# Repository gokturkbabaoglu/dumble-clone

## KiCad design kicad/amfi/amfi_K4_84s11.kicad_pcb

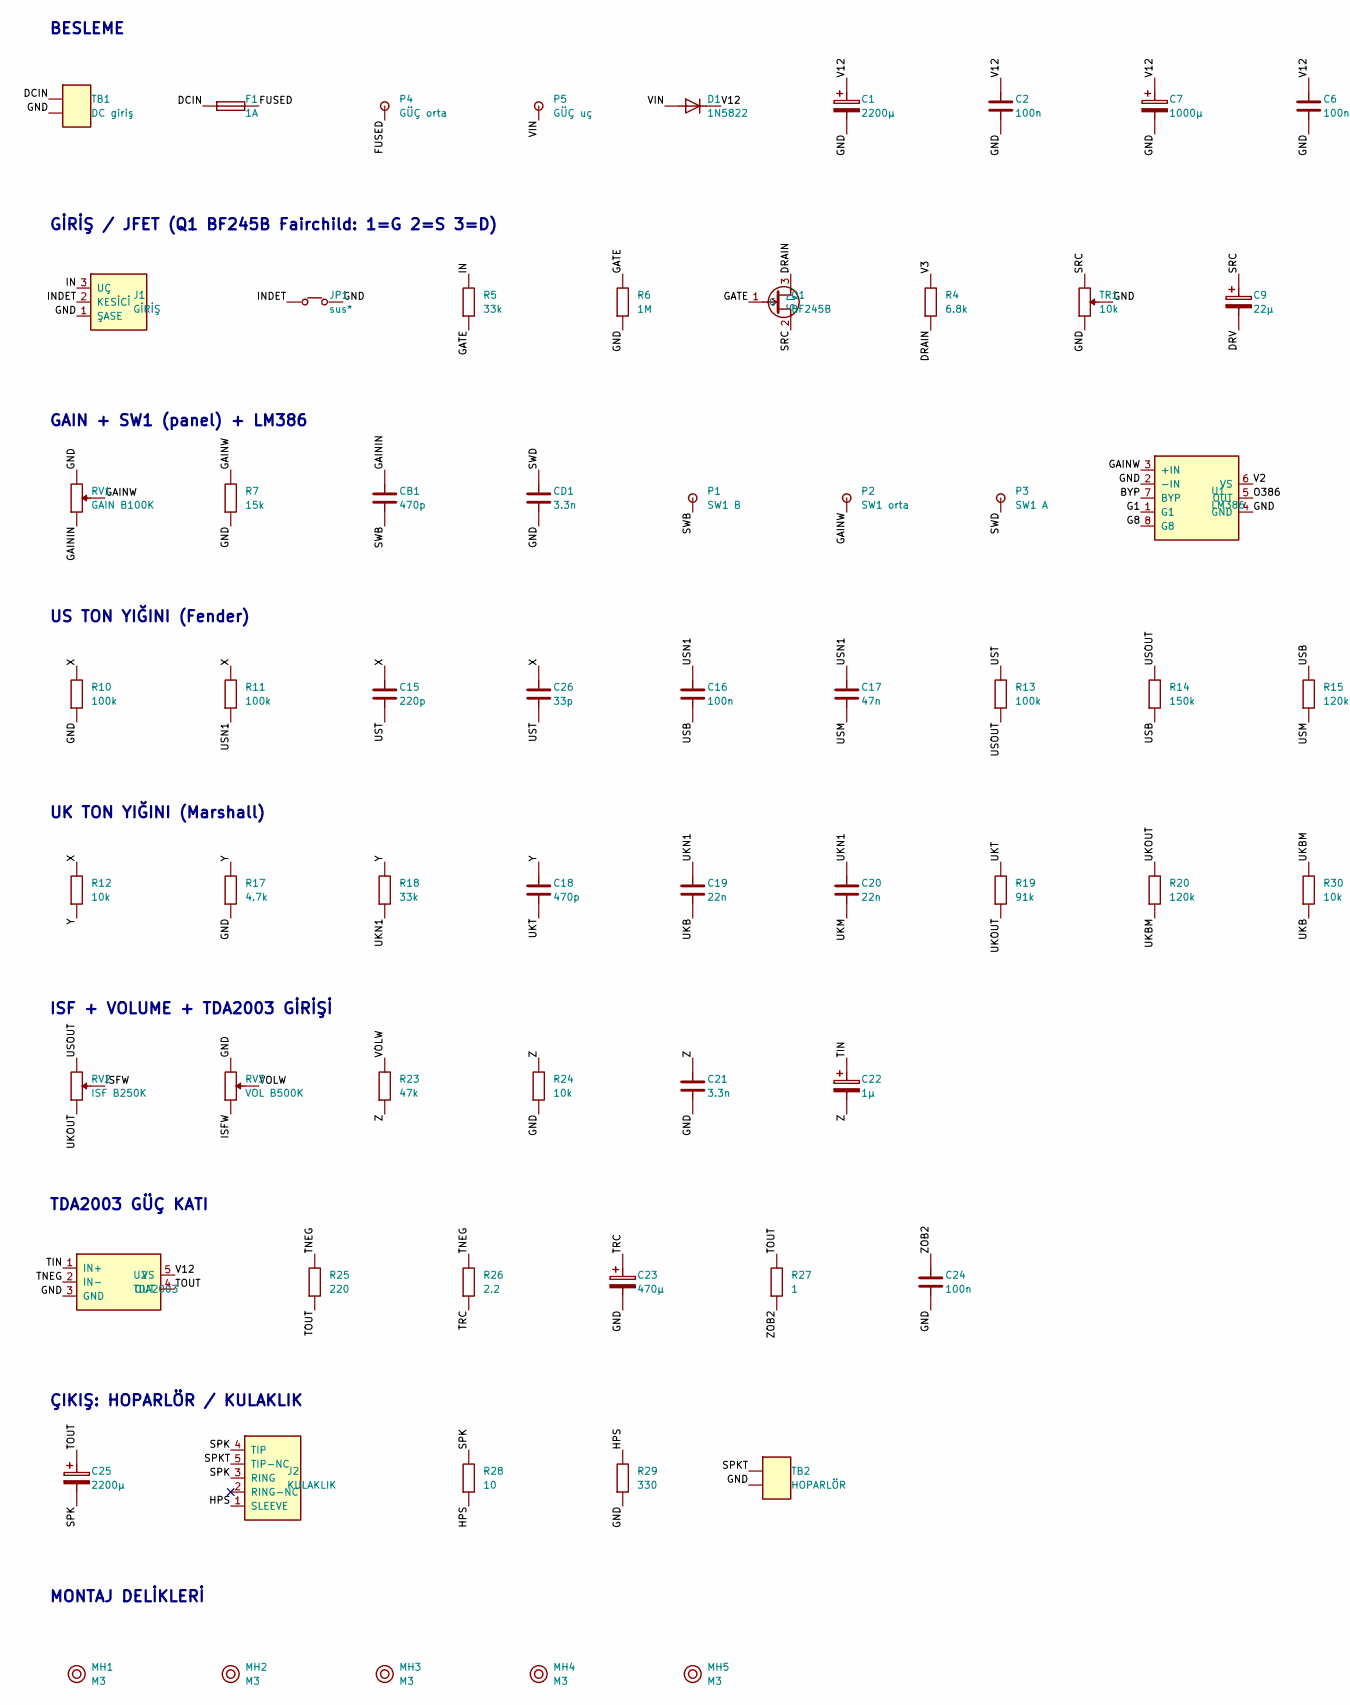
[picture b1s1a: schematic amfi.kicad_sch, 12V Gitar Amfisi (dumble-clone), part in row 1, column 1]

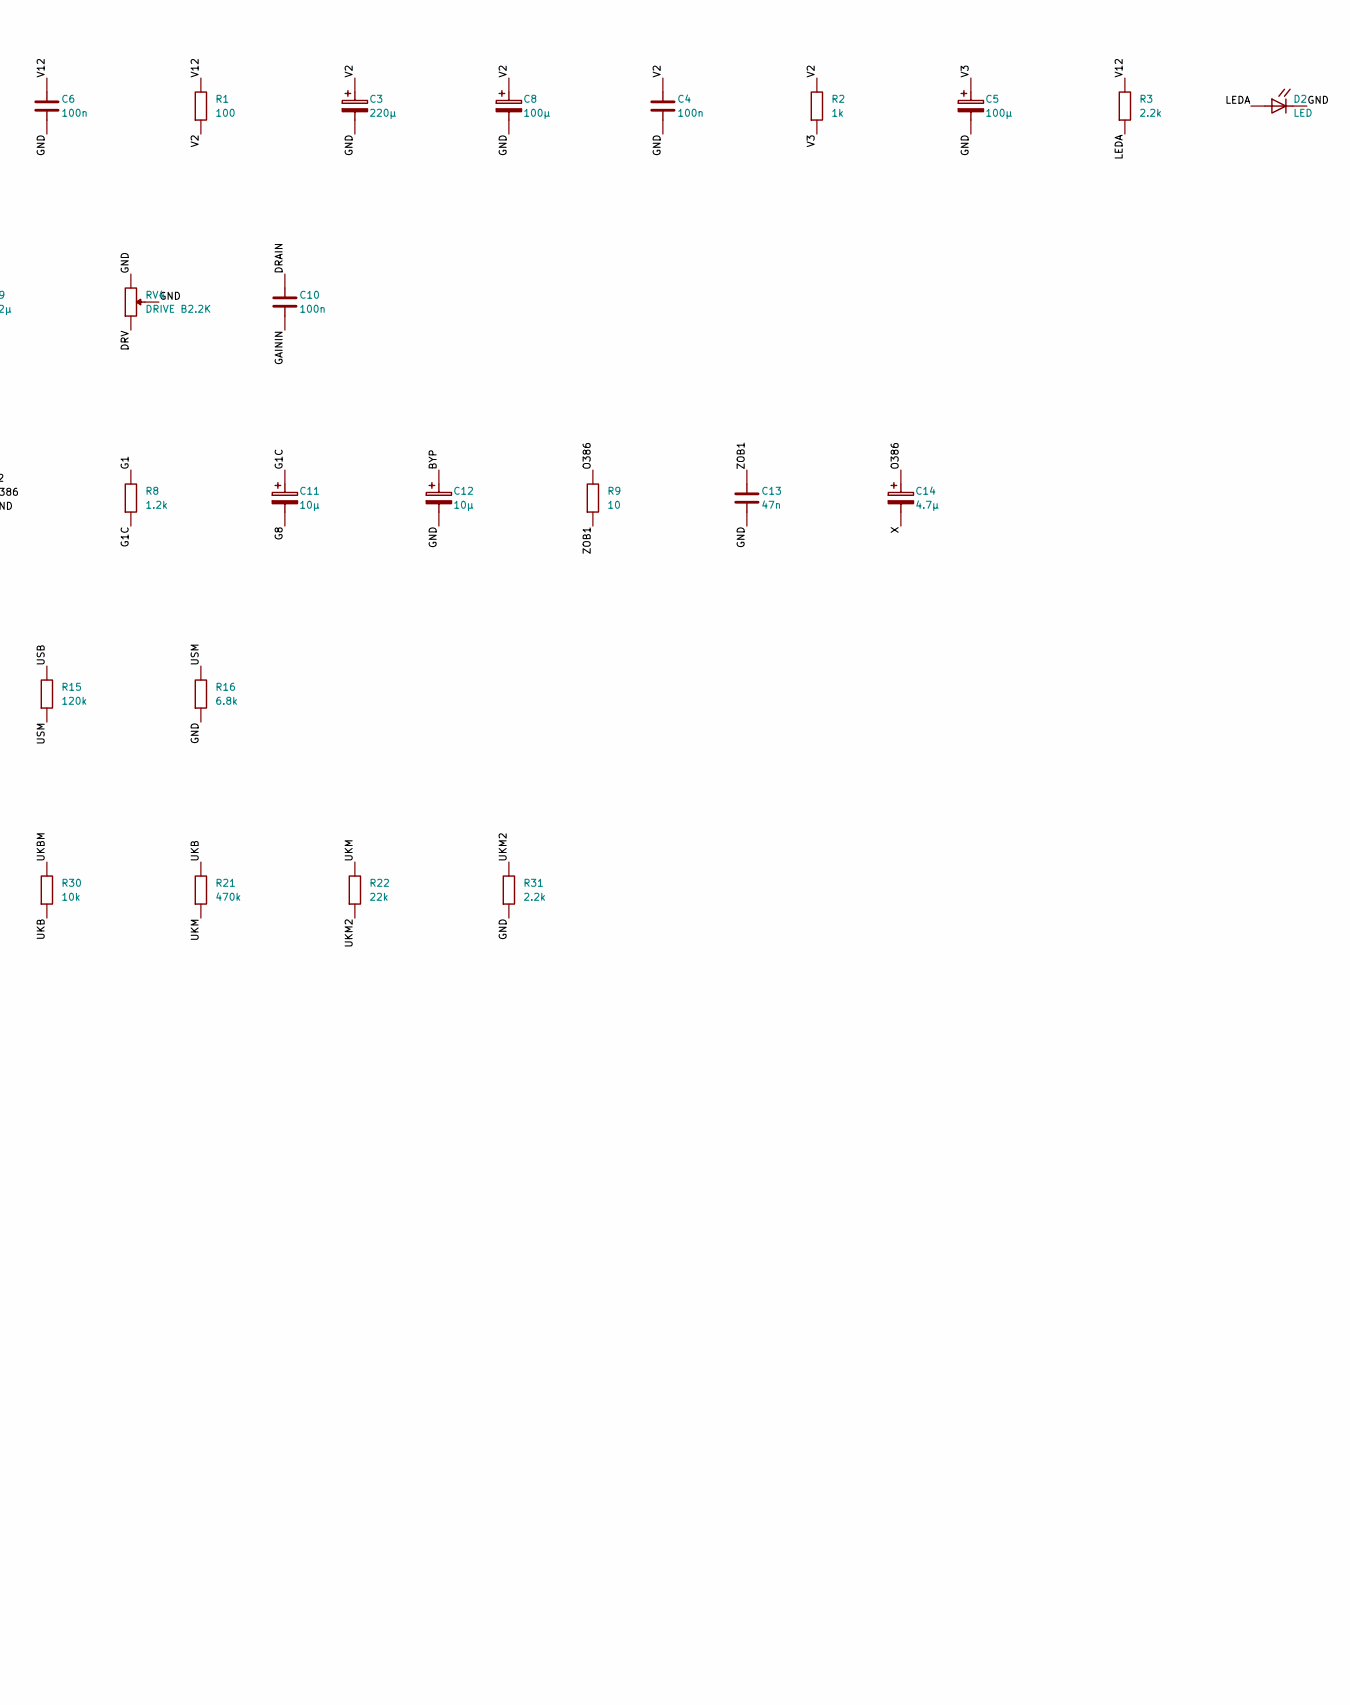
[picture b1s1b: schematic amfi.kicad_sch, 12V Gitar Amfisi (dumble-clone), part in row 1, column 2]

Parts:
C1, C25: 2200µ; CP_D12.5_P5
C2, C4, C6, C10, C16, C24: 100n; C_Film_P5.08
C3: 220µ; CP_D6.3_P2.5
C5, C8: 100µ; CP_D5_P2
C7: 1000µ; CP_D10_P5
C9: 22µ; CP_D5_P2
C11, C12: 10µ; CP_D5_P2
C13, C17: 47n; C_Film_P5.08
C14: 4.7µ; CP_D5_P2
C15: 220p; C_Disc_P5.08
C18: 470p; C_Disc_P5.08
C19, C20: 22n; C_Film_P5.08
C21: 3.3n; C_Film_P5.08
C22: 1µ; CP_D5_P2
C23: 470µ; CP_D8_P3.5
C26: 33p; C_Disc_P5.08
CB1: 470p; C_Disc_P5.08
CD1: 3.3n; C_Film_P5.08
D1: 1N5822; DO201_P15.24
D2: LED; LED_5mm_Dik90
F1: 1A; Sigorta_23x9_P10
J1: GİRİŞ; Jak_6.35_Mono
J2: KULAKLIK; PJ-324M
JP1: sus*; Jumper_P5.08
MH1, MH2, MH3, MH4, MH5: M3; MH_M3
P1: SW1 B; Pad_Kablo
P2: SW1 orta; Pad_Kablo
P3: SW1 A; Pad_Kablo
P4: GÜÇ orta; Pad_Kablo
P5: GÜÇ uç; Pad_Kablo
Q1: BF245B; TO92_Inline_GSD
R1: 100; R_P10.16
R2: 1k; R_P10.16
R3, R31: 2.2k; R_P10.16
R4, R16: 6.8k; R_P10.16
R5, R18: 33k; R_P10.16
R6: 1M; R_P10.16
R7: 15k; R_P10.16
R8: 1.2k; R_P10.16
R9, R28: 10; R_P10.16
R10, R11, R13: 100k; R_P10.16
R12, R24, R30: 10k; R_P10.16
R14: 150k; R_P10.16
R15, R20: 120k; R_P10.16
R17: 4.7k; R_P10.16
R19: 91k; R_P10.16
R21: 470k; R_P10.16
R22: 22k; R_P10.16
R23: 47k; R_P10.16
R25: 220; R_P10.16
R26: 2.2; R_P10.16
R27: 1; R_P10.16
R29: 330; R_P10.16
RV1: GAIN B100K; Pot_WH148_16mm
RV2: ISF B250K; Pot_WH148_16mm
RV3: VOL B500K; Pot_WH148_16mm
RV4: DRIVE B2.2K; Pot_WH148_16mm
TB1: DC giriş; Klemens_2_P5.08
TB2: HOPARLÖR; Klemens_2_P5.08
TR1: 10k; Trim_3296W
U1: LM386; DIP8_Socket
U2: TDA2003; Pentawatt_V

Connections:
BYP: C12.1 (+), U1.7 (BYP)
DCIN: F1.1, TB1.1
DRAIN: C10.1, Q1.3 (D), R4.2
DRV: C9.2 (-), RV4.3
FUSED: F1.2, P4.1
G1: R8.1, U1.1 (G1)
G1C: C11.1 (+), R8.2
G8: C11.2 (-), U1.8 (G8)
GAININ: C10.2, CB1.1, RV1.3
GAINW: P2.1, R7.1, RV1.2, U1.3 (+IN)
GATE: Q1.1 (G), R5.2, R6.1
GND: C1.2 (-), C2.2, C3.2 (-), C4.2, C5.2 (-), C6.2, C7.2 (-), C8.2 (-), C12.2 (-), C13.2, C21.2, C23.2 (-), C24.2, CD1.2, D2.2 (K), J1.1 (ŞASE), JP1.2, R6.2, R7.2, R10.2, R16.2, R17.2, R24.2, R29.2, R31.2, RV1.1, RV3.1, RV4.1, RV4.2, TB1.2, TB2.2, TR1.2, TR1.3, U1.2 (-IN), U1.4 (GND), U2.3 (GND)
HPNC2: J2.2 (RING-NC)
HPS: J2.1 (SLEEVE), R28.2, R29.1
IN: J1.3 (UÇ), R5.1
INDET: J1.2 (KESİCİ), JP1.1
ISFW: RV2.2, RV3.3
LEDA: D2.1 (A), R3.2
O386: C14.1 (+), R9.1, U1.5 (OUT)
SPK: C25.2 (-), J2.3 (RING), J2.4 (TIP), R28.1
SPKT: J2.5 (TIP-NC), TB2.1
SRC: C9.1 (+), Q1.2 (S), TR1.1
SWB: CB1.2, P1.1
SWD: CD1.1, P3.1
TIN: C22.1 (+), U2.1 (IN+)
TNEG: R25.1, R26.1, U2.2 (IN-)
TOUT: C25.1 (+), R25.2, R27.1, U2.4 (OUT)
TRC: C23.1 (+), R26.2
UKB: C19.2, R21.1, R30.2
UKBM: R20.2, R30.1
UKM: C20.2, R21.2, R22.1
UKM2: R22.2, R31.1
UKN1: C19.1, C20.1, R18.2
UKOUT: R19.2, R20.1, RV2.3
UKT: C18.2, R19.1
USB: C16.2, R14.2, R15.1
USM: C17.2, R15.2, R16.1
USN1: C16.1, C17.1, R11.2
USOUT: R13.2, R14.1, RV2.1
UST: C15.2, C26.2, R13.1
V2: C3.1 (+), C4.1, C8.1 (+), R1.2, R2.1, U1.6 (VS)
V3: C5.1 (+), R2.2, R4.1
V12: C1.1 (+), C2.1, C6.1, C7.1 (+), D1.2 (K), R1.1, R3.1, U2.5 (VS)
VIN: D1.1 (A), P5.1
VOLW: R23.1, RV3.2
X: C14.2 (-), C15.1, C26.1, R10.1, R11.1, R12.1
Y: C18.1, R12.2, R17.1, R18.1
Z: C21.1, C22.2 (-), R23.2, R24.1
ZOB1: C13.1, R9.2
ZOB2: C24.1, R27.2

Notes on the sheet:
BESLEME
GİRİŞ / JFET (Q1 BF245B Fairchild: 1=G 2=S 3=D)
GAIN + SW1 (panel) + LM386
US TON YIĞINI (Fender)
UK TON YIĞINI (Marshall)
ISF + VOLUME + TDA2003 GİRİŞİ
TDA2003 GÜÇ KATI
ÇIKIŞ: HOPARLÖR / KULAKLIK
MONTAJ DELİKLERİ

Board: 2 copper layers, 85 parts (0 on the bottom side), 49 nets, no tracks yet.
